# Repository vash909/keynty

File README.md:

# KEYNTY CMOS CW Keyer
A CW keyer based on the original Minty Keyer project by K4ICY https://www.k4icy.com/weekend_radio_minty_kool_keyer.html

Improvements:
- Removed diodes OR
- Removed BJT keying for OR matrix
- Added CMOS OR Gates
- Changed all the logic gates to Low-Voltage (3.6V max)
- Added sidetone buzzer
- Added power LED
- Added alkaline battery holder (3V AA size x2)
- Reduced overall power consumption
- Added a switch for switching iambic mode (A/B)
- Added a switch for sidetone enable

PCB can be mounted directly on the back of the battery holder.

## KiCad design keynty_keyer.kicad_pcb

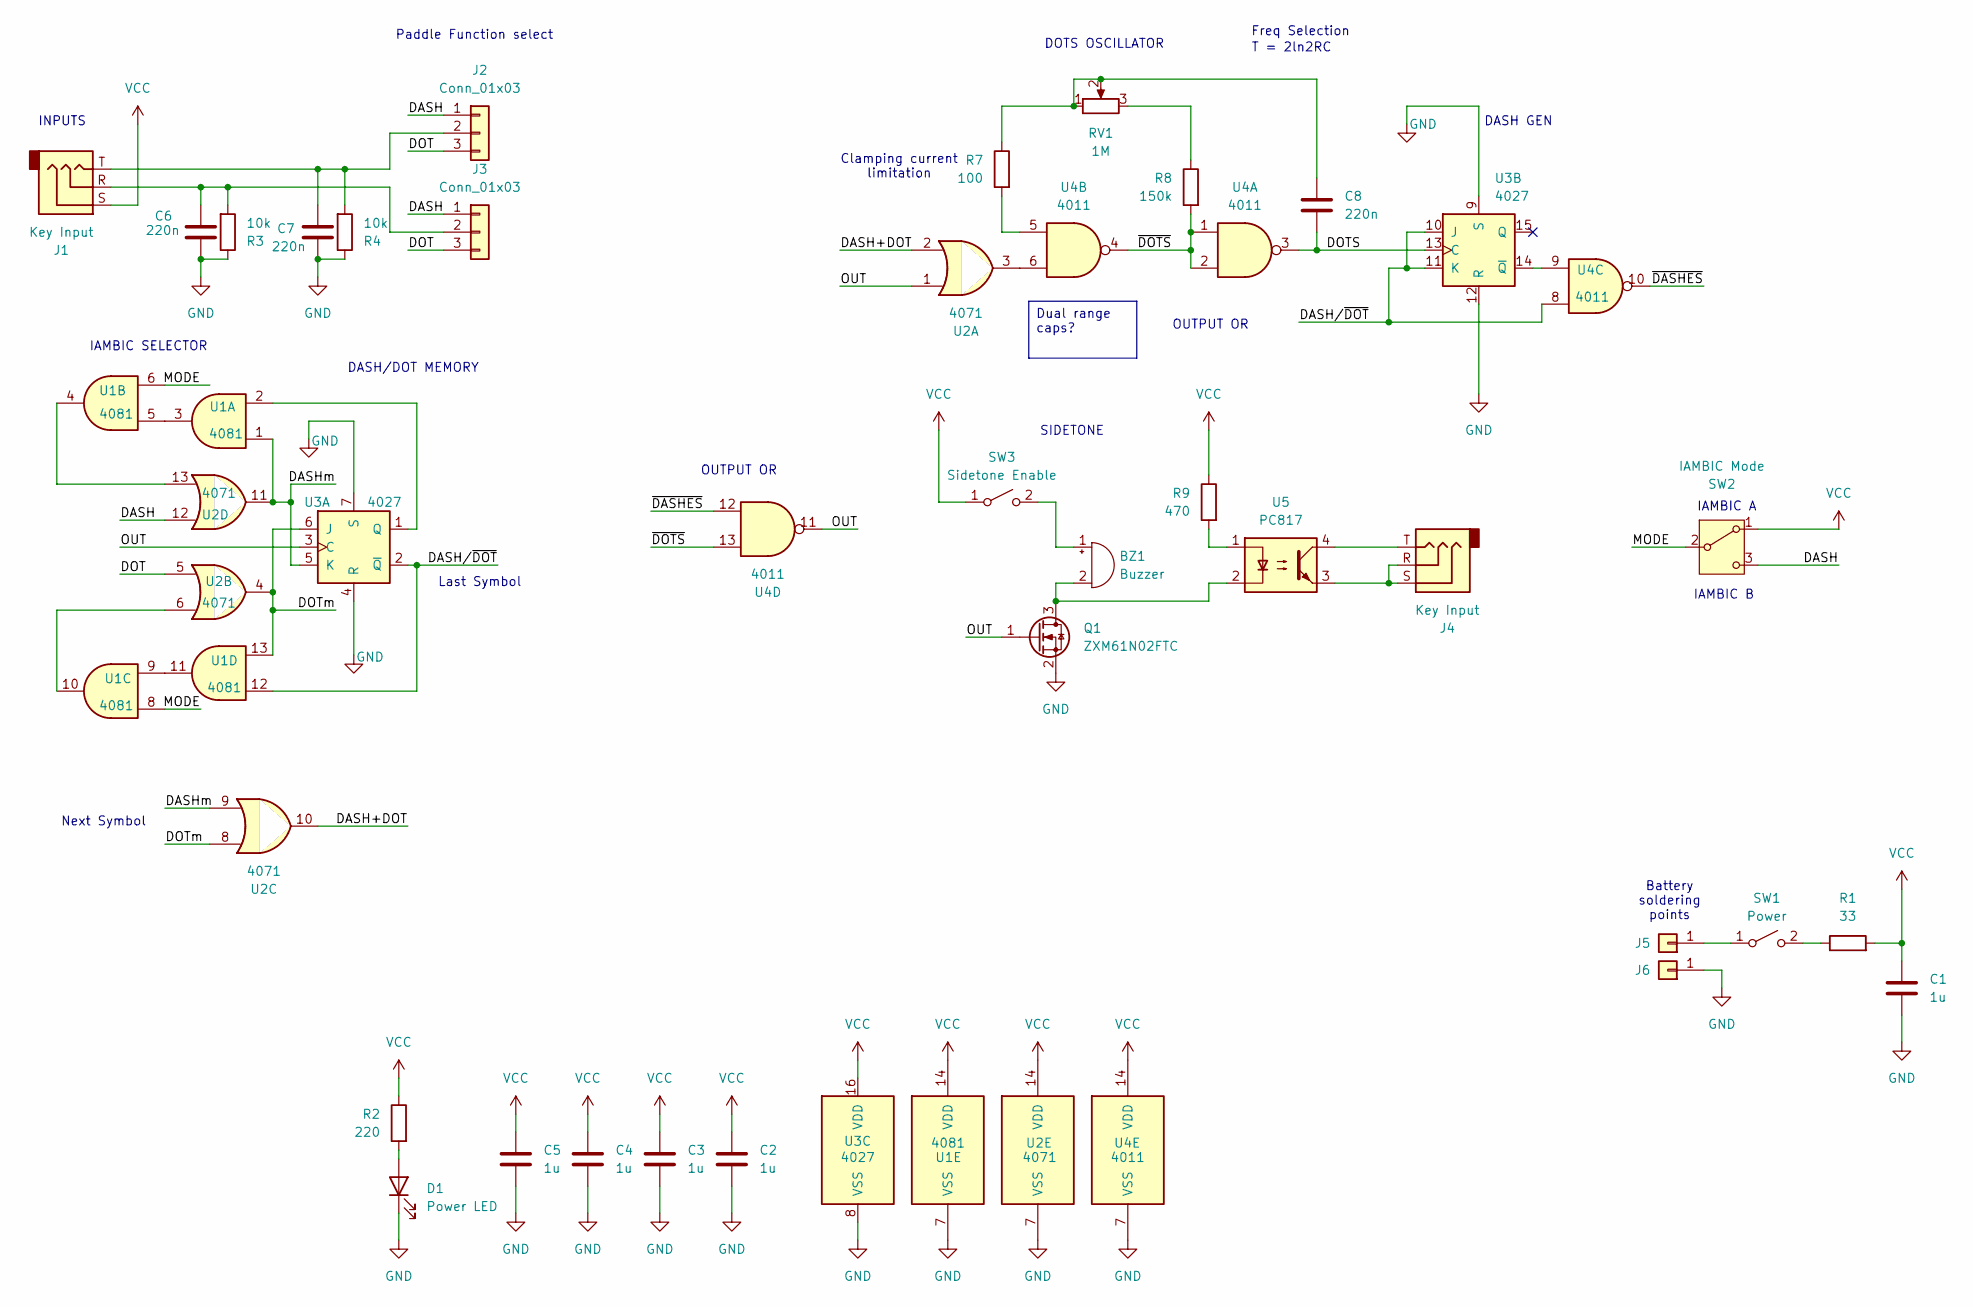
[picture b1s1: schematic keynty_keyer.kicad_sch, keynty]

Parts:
BZ1: Buzzer; Buzzer_12x9.5RM7.6; LCSC C49246930
C1, C2, C3, C4, C5: 1u; C_0805_2012Metric; LCSC C28323
C6, C7, C8: 220n; C_0603_1608Metric; LCSC C21120
D1: Power LED; LED_0603_1608Metric; LCSC C2286
J1, J4: Key Input; Jack_3.5mm_CUI_SJ1-3513N_Horizontal; LCSC C22355739
J2, J3: Conn_01x03; PinHeader_1x03_P2.54mm_Vertical; LCSC C2691448
J5, J6: Conn_01x01; TestPoint_THTPad_2.0x2.0mm_Drill1.0mm; LCSC C2691448
Q1: ZXM61N02FTC; SOT-23; LCSC C19632264
R1: 33; R_0603_1608Metric; LCSC C23140
R2: 220; R_0603_1608Metric; LCSC C22962
R3, R4: 10k; R_0603_1608Metric; LCSC C25804
R7: 100; R_0603_1608Metric; LCSC C22775
R8: 150k; R_0603_1608Metric; LCSC C22807
R9: 470; R_0603_1608Metric; LCSC C23179
RV1: 1M; Potentiometer_Alps_RK09K_Single_Vertical
SW1: Power; SW_Slide_SPDT_Straight_CK_OS102011MS2Q
SW2: IAMBIC Mode; SW_Slide_SPDT_Straight_CK_OS102011MS2Q
SW3: Sidetone Enable; SW_Slide_SPDT_Straight_CK_OS102011MS2Q
U1: 4081; SOIC-14_3.9x8.7mm_P1.27mm; LCSC C52342
U2: 4071; SOIC-14_3.9x8.7mm_P1.27mm; LCSC C28869
U3: 4027; SOIC-16_3.9x9.9mm_P1.27mm; LCSC C157536
U4: 4011; SOIC-14_3.9x8.7mm_P1.27mm; LCSC C6725
U5: PC817; DIP-4_W8.89mm_SMDSocket_LongPads; LCSC C41807

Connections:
/DASH: J2.1, J3.1, SW2.3 (C), U2.12
/DASH+DOT: U2.2, U2.10
/DASHm: U1.1, U2.9, U2.11, U3.5 (K)
/DASH/~DOT: U1.12, U3.2 (~Q), U3.10 (J), U3.11 (K), U4.8
/DOT: J2.3, J3.3, U2.5
/DOTS: C8.2, U3.13 (C), U4.3
/DOTm: U1.13, U2.4, U2.8, U3.6 (J)
/MODE: SW2.2 (B), U1.6, U1.8
/OUT: Q1.1 (G), U2.1, U3.3 (C), U4.11
/~DASHES: U4.10, U4.12
/~DOTS: R8.2, U4.1, U4.2, U4.4, U4.13
GND: C1.2, C2.2, C3.2, C4.2, C5.2, C6.1, C7.1, D1.1 (K), J6.1 (Pin_1_1), Q1.2 (S), R3.1, R4.1, U1.7 (VSS), U2.7 (VSS), U3.4 (R), U3.7 (S), U3.8 (VSS), U3.9 (S), U3.12 (R), U4.7 (VSS)
unnamed: BZ1.1 (+), SW3.2 (B)
unnamed: BZ1.2 (-), Q1.3 (D), U5.2
unnamed: C8.1, R7.1, RV1.1, RV1.2
unnamed: D1.2 (A), R2.2
unnamed: C7.2, J1.T, J2.2, R4.2
unnamed: C6.2, J1.R, J3.2, R3.2
unnamed: J4.R, J4.S, U5.3
unnamed: J4.T, U5.4
unnamed: J5.1 (Pin_1_1), SW1.1 (A)
unnamed: R7.2, U4.5
unnamed: R8.1, RV1.3
unnamed: R9.2, U5.1
unnamed: R1.1, SW1.2 (B)
unnamed: U1.3, U1.5
unnamed: U1.4, U2.13
unnamed: U1.10, U2.6
unnamed: U1.9, U1.11
unnamed: U2.3, U4.6
unnamed: U1.2, U3.1 (Q)
unnamed: U3.14 (~Q), U4.9
VCC: C1.1, C2.1, C3.1, C4.1, C5.1, J1.S, R1.2, R2.1, R9.1, SW2.1 (A), SW3.1 (A), U1.14 (VDD), U2.14 (VDD), U3.16 (VDD), U4.14 (VDD)

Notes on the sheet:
Freq Selection
IAMBIC SELECTOR
DASH/DOT MEMORY
Battery soldering points
OUTPUT OR
DASH GEN
Last Symbol
IAMBIC B
T = 2ln2RC
SIDETONE
INPUTS
Paddle Function select
Next Symbol
Clamping current limitation
DOTS OSCILLATOR
IAMBIC A
Dual range caps?

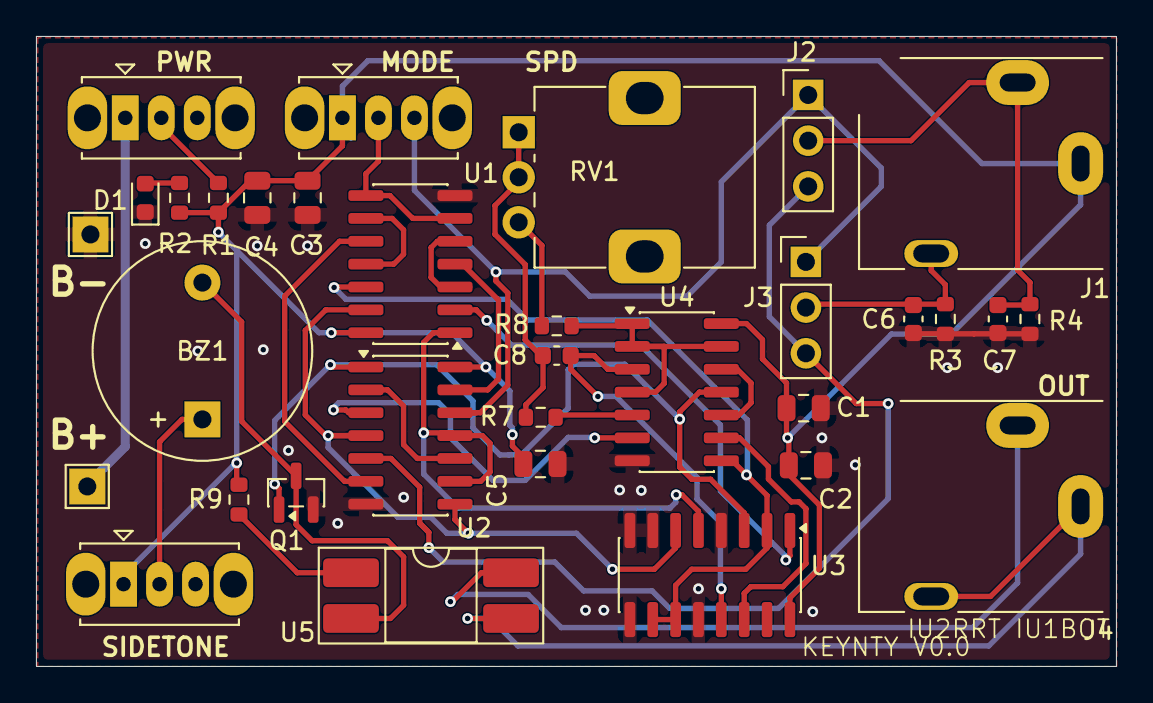
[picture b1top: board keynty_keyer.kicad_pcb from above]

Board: 2 copper layers, 60.0 x 35.0 mm, 33 parts (0 on the bottom side), 33 nets.

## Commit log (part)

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2026-04-03 created files
2026-04-03 added power conditioning
2026-04-05 First Draft of schematic, starting from minty keyer, removed all the diode logic, changed output and input stages
2026-04-07 added selector dot/dash, verified oscillator frequencies, added buzzer placeholder
2026-04-07 added matteo sidetononi e matteo powerleddoni
2026-04-07 corrected IAMBIC selector,added footprints, first PCB Draft
2026-04-07 changed output jack connections, corrected mosfet
2026-04-07 added reference datasheets in BOM
2026-04-07 correct powwer supply inverted
2026-04-07 changed pull down ok the inputs
2026-04-10 refdes position adjusted and clean-up back silkscreen
2026-04-10 Revise README for KEYNTY CMOS CW Keyer
    Updated project name and added detailed improvements and controls.
2026-04-10 added missing resistor values for pull-down and opto drive
2026-04-10 corrected battery footprint, added QR, changed minor silkscreen
